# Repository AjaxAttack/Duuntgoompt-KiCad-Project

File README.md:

# Duuntgoompt-KiCad-Project
## This repo is the Duuntgoompt project files home.
### The Duuntgoompt PCB, with features:
- Esp32s3 based system
- Wifi & Bluetooth compatible
- USB C
- 1x26 Pin M Connections Suitable for breadboard plug-n-use
- Solder Bridge LED Indicators
- Qwiic I2C Connectors for other sensor modules
### Duuntgoompt - Blender Full Render

### Duuntgoompt Overhead

### Top-level Schematic Image

### Power Schematic 

### Connectors Schematic

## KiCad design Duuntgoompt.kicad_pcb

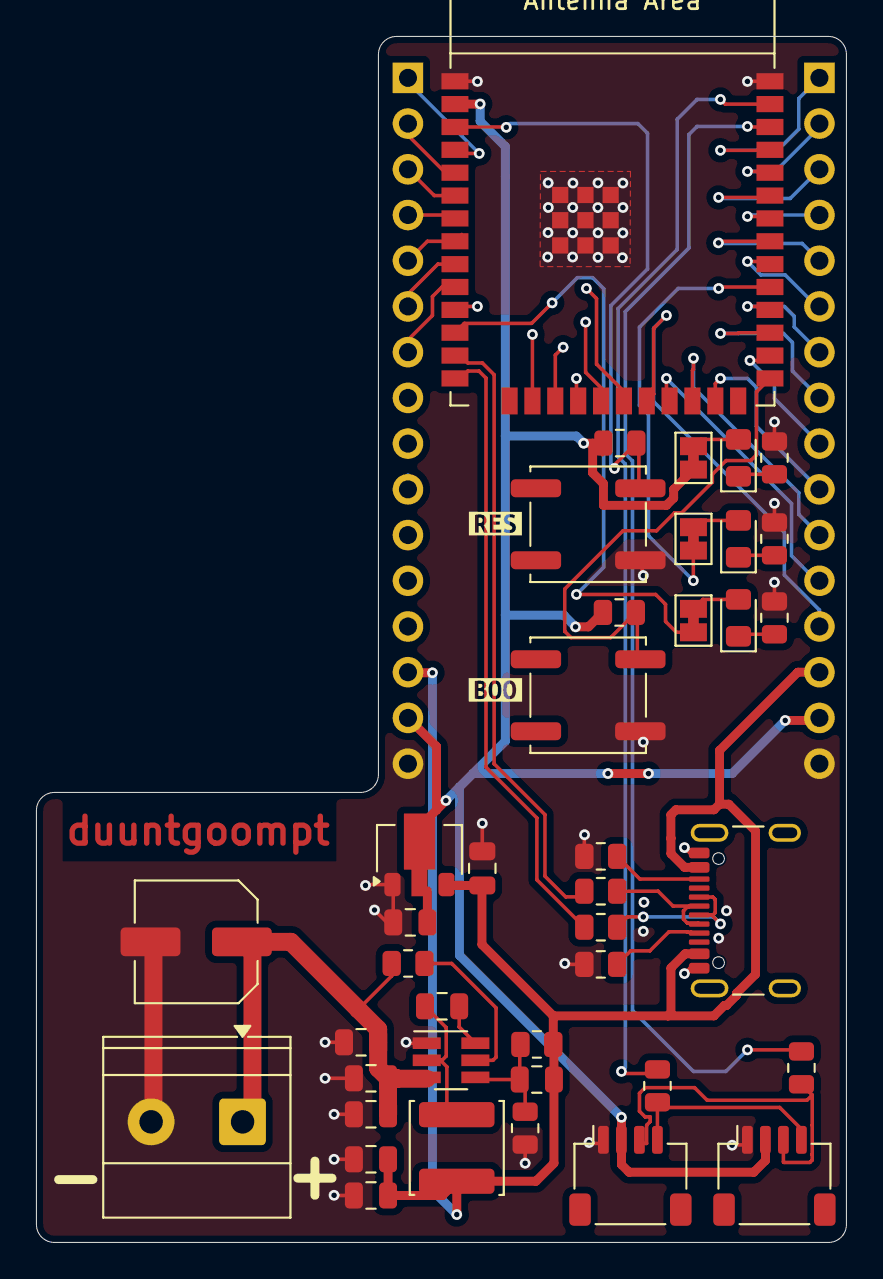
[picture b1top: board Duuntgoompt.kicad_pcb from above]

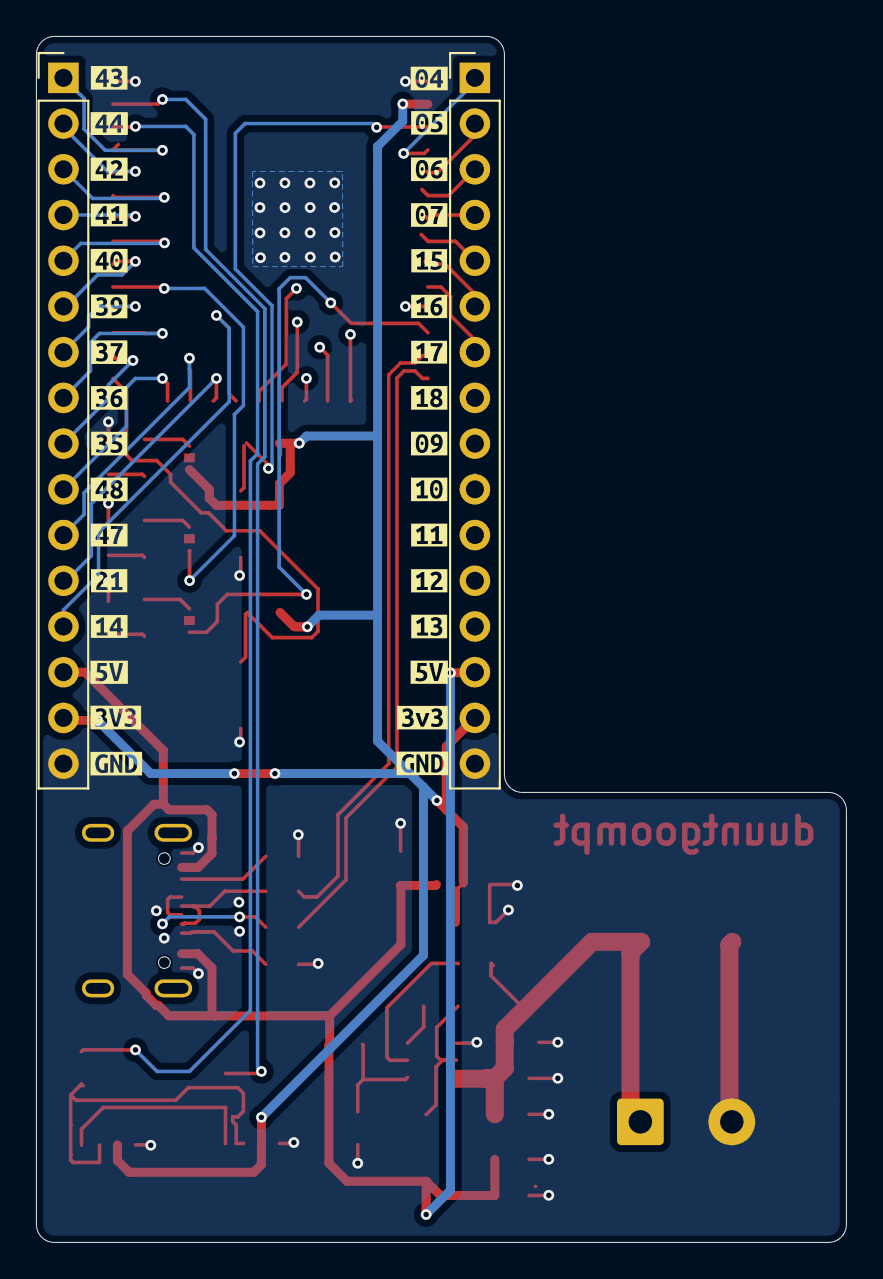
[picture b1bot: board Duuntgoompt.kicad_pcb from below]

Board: 4 copper layers, 45.0 x 67.0 mm, 76 parts (34 on the bottom side), 54 nets.

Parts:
C1: RGA221M1EBK-0811G; C_Elec_6.3x7.7
C2, C3, C4, C6, C7, C8, C9, C10, C11: CL21A226MQQNNNE; C_0805_2012Metric
D1, D2, D3: LED; LED_0805_2012Metric_Pad1.15x1.40mm_HandSolder
J1, J2: SW_Push_1P1T_NO_CK_KSC7xxJ
J3, J6: I2C_STANDARDQWIIC; JST_SH_SM04B-SRSS-TB_1x04-1MP_P1.00mm_Horizontal
J4, J8: Conn_01x13_Pin; PinHeader_1x16_P2.54mm_Vertical
J5: USB4520-03-0-A_REVA; USB_C_Receptacle_GCT_USB4105-xx-A_16P_TopMnt_Horizontal
J7: TerminalBlock_Phoenix_MKDS-1,5-2-5.08_1x02_P5.08mm_Horizont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
JP1, JP2, JP3: SolderJumper_2_Bridged; SolderJumper-2_P1.3mm_Bridged_Pad1.0x1.5mm
L1: SRP3212A-4R7M; L_Changjiang_FNR5020S
R1, R2, R3, R4, R5, R6, R7, R8, R9, R10, R11: RESISTOR0603; R_0805_2012Metric
R12, R13, R14: RC0603FR-7W10KL; R_0805_2012Metric
U1: ESP32-S3-WROOM-1
U2: AZ1117C; SOT-89-3
U3: TPS562208; SOT-23-6_Handsoldering
kibuzzard-66ABEB3C: G***; kibuzzard-66ABEB3C
kibuzzard-66ABEB4E: G***; kibuzzard-66ABEB4E
kibuzzard-66ABEB5B: G***; kibuzzard-66ABEB5B
kibuzzard-66ABEB61: G***; kibuzzard-66ABEB61
kibuzzard-66ABEB82: G***; kibuzzard-66ABEB82
kibuzzard-66ABEB90: G***; kibuzzard-66ABEB90
kibuzzard-66ABEB98: G***; kibuzzard-66ABEB98
kibuzzard-66ABEBCB: G***; kibuzzard-66ABEBCB
kibuzzard-66ABEBD1: G***; kibuzzard-66ABEBD1
kibuzzard-66ABEBD9: G***; kibuzzard-66ABEBD9
kibuzzard-66ABEBE3: G***; kibuzzard-66ABEBE3
kibuzzard-66ABEBEC: G***; kibuzzard-66ABEBEC
kibuzzard-66ABEC0B: G***; kibuzzard-66ABEC0B
kibuzzard-66ABEC03: G***; kibuzzard-66ABEC03
kibuzzard-66ABEC20: G***; kibuzzard-66ABEC20
kibuzzard-66ABEC54: G***; kibuzzard-66ABEC54
kibuzzard-66ABED0C: G***; kibuzzard-66ABED0C
kibuzzard-66ABED1D: G***; kibuzzard-66ABED1D
kibuzzard-66ABED4A: G***; kibuzzard-66ABED4A
kibuzzard-66ABED5B: G***; kibuzzard-66ABED5B
kibuzzard-66ABED8D: G***; kibuzzard-66ABED8D
kibuzzard-66ABED29: G***; kibuzzard-66ABED29
kibuzzard-66ABED39: G***; kibuzzard-66ABED39
kibuzzard-66ABED41: G***; kibuzzard-66ABED41
kibuzzard-66ABED51: G***; kibuzzard-66ABED51
kibuzzard-66ABED62: G***; kibuzzard-66ABED62
kibuzzard-66ABED69: G***; kibuzzard-66ABED69
kibuzzard-66ABED70: G***; kibuzzard-66ABED70
kibuzzard-66ABED86: G***; kibuzzard-66ABED86
kibuzzard-66ABEDA4: G***; kibuzzard-66ABEDA4
kibuzzard-66ABEDAC: G***; kibuzzard-66ABEDAC
kibuzzard-66ABEDF7: G***; kibuzzard-66ABEDF7
kibuzzard-66ABF63C: G***; kibuzzard-66ABF63C
kibuzzard-66ABF633: G***; kibuzzard-66ABF633

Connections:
+3.3V: C2.1, J3.2 (VCC), J4.15, J6.2 (VCC), J8.15, JP3.1 (A), R1.2, R2.2, U1.2 (3V3), U2.2 (out)
+5V: C3.1, C4.1, C6.1, C7.1, J4.14, J5.A4, J5.B4, J8.14, L1.1, R13.1, U2.3 (in)
+BATT: C1.1 (+), C8.2, C9.2, C10.2, J7.1 (+), R12.2, U3.3 (Vin)
GND: C1.2 (-), C2.2, C3.2, C6.2, C7.2, C8.1, C9.1, C10.1, J1.1, J2.1, J3.1 (GND), J4.16, J5.A1 (GND_A), J5.B1, J6.1 (GND), J7.2 (-), J8.16, R5.1, R6.1, R7.1, R8.2, R9.2, R14.1, U1.1 (GND), U1.40 (GND), U1.41 (GND), U2.1 (adj), U3.1 (GND)
GPIO4: J4.1, U1.4 (GPIO4/TOUCH4/ADC1_CH3)
GPIO5: J4.2, U1.5 (GPIO5/TOUCH5/ADC1_CH4)
GPIO6: J4.3, U1.6 (GPIO6/TOUCH6/ADC1_CH5)
GPIO7: J4.4, U1.7 (GPIO7/TOUCH7/ADC1_CH6)
GPIO8: JP1.1 (A), U1.12 (GPIO8/TOUCH8/ADC1_CH7/SUBSPICS1)
GPIO9: J4.9, U1.17 (GPIO9/TOUCH9/ADC1_CH8/FSPIHD/SUBSPIHD)
GPIO10: J4.10, U1.18 (GPIO10/TOUCH10/ADC1_CH9/FSPICS0/FSPIIO4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)
GPIO11: J4.11, U1.19 (GPIO11/TOUCH11/ADC2_CH0/FSPID/FSPIIO5/S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)
GPIO12: J4.12, U1.20 (GPIO12/TOUCH12/ADC2_CH1/FSPICLK/FSPIIO6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)
GPIO13: J4.13, U1.21 (GPIO13/TOUCH13/ADC2_CH2/FSPIQ/FSPIIO7/S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)
GPIO14: J8.13, U1.22 (GPIO14/TOUCH14/ADC2_CH3/FSPIWP/FSPIDQS/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)
GPIO15: J4.5, U1.8 (GPIO15/U0RTS/ADC2_CH4/XTAL_32K_P)
GPIO16: J4.6, U1.9 (GPIO16/U0CTS/ADC2_CH5/XTAL_32K_N)
GPIO17: J4.7, U1.10 (GPIO17/U1TXD/ADC2_CH6)
GPIO18: J4.8, U1.11 (GPIO18/U1RXD/ADC2_CH7/CLK_OUT3)
GPIO21: J8.12, U1.23 (GPIO21)
GPIO35: J8.9, U1.28 (SPIIO6/GPIO35/FSPID/SUBSPID)
GPIO36: J8.8, U1.29 (SPIIO7/GPIO36/FSPICLK/SUBSPICLK)
GPIO37: J8.7, U1.30 (SPIDQS/GPIO37/FSPIQ/SUBSPIQ)
GPIO38: JP2.1 (A), U1.31 (GPIO38/FSPIWP/SUBSPIWP)
GPIO39: J8.6, U1.32 (MTCK/GPIO39/CLK_OUT3/SUBSPICS1)
GPIO40: J8.5, U1.33 (MTDO/GPIO40/CLK_OUT2)
GPIO41: J8.4, U1.34 (MTDI/GPIO41/CLK_OUT1)
GPIO42: J8.3, U1.35 (MTMS/GPIO42)
GPIO43: J8.1, U1.37 (U0TXD/GPIO43/CLK_OUT1)
GPIO44: J8.2, U1.36 (U0RXD/GPIO44/CLK_OUT2)
GPIO47: J8.11, U1.24 (GPIO47/SPICLK_P/SUBSPICLK_P_DIFF)
GPIO48: J8.10, U1.25 (GPIO48/SPICLK_N/SUBSPICLK_N_DIFF)
unnamed: D1.2 (A), JP1.2 (B)
unnamed: D1.1 (K), R5.2
unnamed: D2.2 (A), JP2.2 (B)
unnamed: D2.1 (K), R6.2
unnamed: D3.2 (A), JP3.2 (B)
unnamed: D3.1 (K), R7.2
unnamed: J3.4 (SCL), J6.4 (SCL), R3.1
unnamed: J3.3 (SDA), J6.3 (SDA), R4.1
unnamed: J5.A5 (CC1), R8.1
unnamed: J5.B5 (CC2), R9.1
unnamed: J5.A7 (DN1), J5.B7 (DN2), R11.1
unnamed: J5.A6 (DP1), J5.B6 (DP2), R10.1
unnamed: J1.2, R1.1, U1.3 (EN)
unnamed: J2.2, R2.1, U1.27 (GPIO0/BOOT)
unnamed: R12.1, U3.5 (EN)
unnamed: C11.1, L1.2, U3.2 (SW)
unnamed: C11.2, U3.6 (VBST)
unnamed: C4.2, R13.2, R14.2, U3.4 (VFB)
scl: R3.2, U1.39 (GPIO1/TOUCH1/ADC1_CH0)
sda: R4.2, U1.38 (GPIO2/TOUCH2/ADC1_CH1)
usb_d+: R10.2, U1.14 (GPIO20/U1CTS/ADC2_CH9/CLK_OUT1/USB_D+)
usb_d-: R11.2, U1.13 (GPIO19/U1RTS/ADC2_CH8/CLK_OUT2/USB_D-)

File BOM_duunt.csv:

"Id";"Designator";"Footprint";"Quantity";"Designation";"Supplier and ref";
1;"U2";"SOT-89-3";1;"AZ1117C";;;
2;"C10,C3,C4,C2,C11,C6,C9,C8,C7";"C_0805_2012Metric";9;"CL21A226MQQNNNE";;;
3;"R9,R7,R1,R3,R6,R8,R5,R10,R11,R4,R2";"R_0805_2012Metric";11;"RESISTOR0603";;;
4;"JP2,JP1,JP3";"SolderJumper-2_P1.3mm_Bridged_Pad1.0x1.5mm";3;"SolderJumper_2_Bridged";;;
5;"R13,R14,R12";"R_0805_2012Metric";3;"RC0603FR-7W10KL";;;
6;"U1";"ESP32-S3-WROOM-1";1;"ESP32-S3-WROOM-1";;;
7;"J2,J1";"PTS526SM08SMTR2LFS";2;"~";;;
8;"J3,J6";"1X04_1MM_RA";2;"I2C_STANDARDQWIIC";;;
9;"C1";"C_Elec_6.3x7.7";1;"RGA221M1EBK-0811G";;;
10;"D3,D2,D1";"LED_0805_2012Metric_Pad1.15x1.40mm_HandSolder";3;"LED";;;
11;"J7";"TerminalBlock_bornier-2_P5.08mm";1;"~";;;
12;"J5";"GCT_USB4520-03-0-A_REVA";1;"USB4520-03-0-A_REVA";;;
13;"L1";"L_Changjiang_FNR5020S";1;"SRP3212A-4R7M";;;
14;"U3";"SOT-23-6_Handsoldering";1;"TPS562208";;;
15;"J8,J4";"PinHeader_1x16_P2.54mm_Vertical";2;"Conn_01x13_Pin";;;

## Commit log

2026-03-21 initial comment
2026-03-22 added some stuff to schematic and PCB design
2026-03-22 added the gitignore file
2026-03-22 all DRC errors are cleared
